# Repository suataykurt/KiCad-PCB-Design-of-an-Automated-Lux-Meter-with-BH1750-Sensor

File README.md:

# KiCad-PCB-Design-of-an-Automated-Lux-Meter

This repository contains the PCB design, schematic, and 3D visualization of a digital Lux Meter project, developed using KiCad. The system utilizes the **BH1750** ambient light sensor and an **I2C LCD** display for real-time light intensity monitoring.

## 📋 Project Overview
The project involves the complete design cycle for a light-measuring device, from schematic entry to PCB layout and 3D visualization. It demonstrates how to integrate I2C-based sensors with an Arduino-based controller to create a compact, functional measurement tool.

## 🛠 Design Highlights
* **Schematic Design:** Integration of the BH1750 light sensor, I2C LCD interface, and Arduino Nano controller.
* **PCB Layout:** Custom-designed PCB layout in KiCad, focusing on signal integrity and component placement.
* **3D Visualization:** In-depth examination of the 3D model for physical form factor and footprint validation.
* **Power Management:** On-board voltage regulation (AMS1117-5.0) ensuring stable operation.

## 🚀 Key Features
* **BH1750 Sensor Integration:** High-precision ambient light measurement.
* **Interactive Interface:** I2C LCD for clear, real-time data display.
* **Professional CAD Standards:** Industry-standard PCB design practices.

## 📂 Repository Contents
* `lux_olcer.kicad_sch`: Schematic file.
* `lux_olcer.kicad_pcb`: PCB layout design file.
* `lux_olcer.kicad_pro`: KiCad project settings.
* `BH1750.jpg` / `I2C-LCD.jpg`: Component reference images.

## 💡 How to Access
1. Clone the repository and open the project using **KiCad**.
2. Explore the PCB layout to view routing and component placement.
3. Use the KiCad 3D Viewer to inspect the hardware assembly models.

---
*Developed by Suat AYKURT | Zonguldak Bülent Ecevit University*

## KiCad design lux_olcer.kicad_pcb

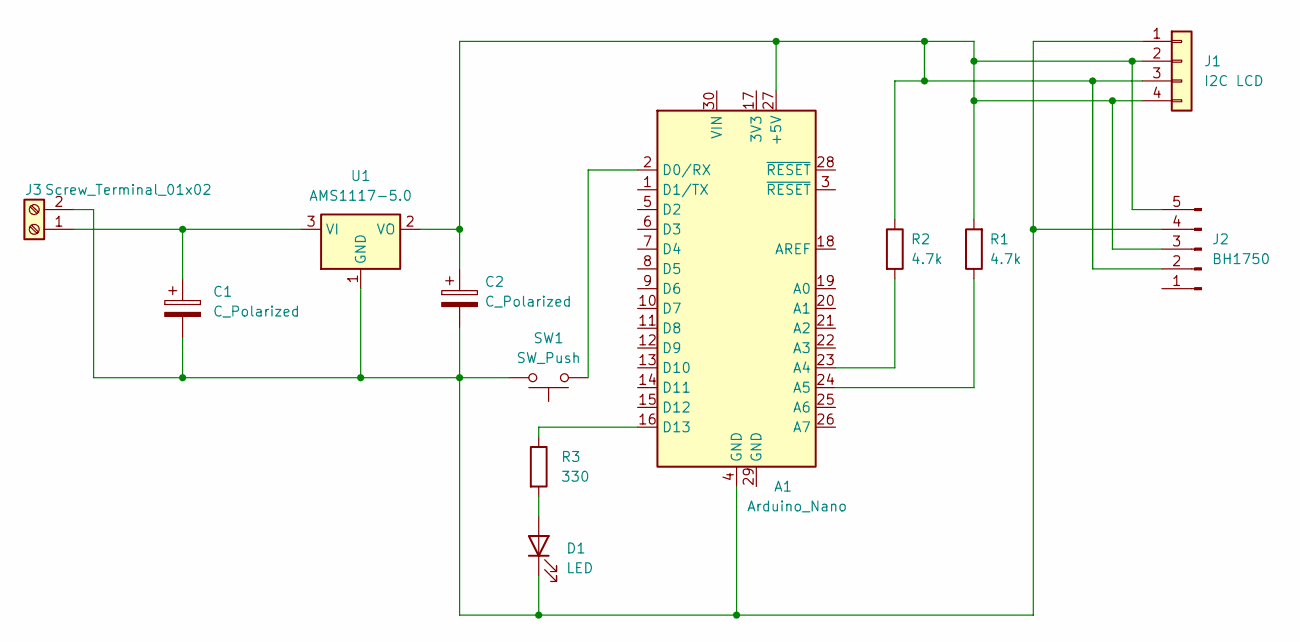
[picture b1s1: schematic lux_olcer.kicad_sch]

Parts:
A1: Arduino_Nano
C1, C2: C_Polarized; CP_Radial_D5.0mm_P2.00mm
D1: LED; LED_D5.0mm
J1: I2C LCD; PinHeader_1x04_P2.54mm_Vertical
J2: BH1750; PinHeader_1x05_P2.54mm_Vertical
J3: Screw_Terminal_01x02; TerminalBlock_Phoenix_MKDS-1,5-2_1x02_P5.00mm_Horizontal
R1, R2: 4.7k; R_Axial_DIN0207_L6.3mm_D2.5mm_P7.62mm_Horizontal
R3: 330; R_Axial_DIN0207_L6.3mm_D2.5mm_P7.62mm_Horizontal
SW1: SW_Push; SW_PUSH_6mm
U1: AMS1117-5.0; TO-220-3_Vertical

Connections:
unnamed: A1.27 (+5V), C2.1, J1.2, J1.3, J1.4, J2.2, J2.3, J2.5, R1.2, R2.1, U1.2 (VO)
unnamed: A1.23 (A4), R2.2
unnamed: A1.24 (A5), R1.1
unnamed: A1.2 (D0/RX), SW1.1
unnamed: A1.16 (D13), R3.1
unnamed: D1.2 (A), R3.2
unnamed: A1.4 (GND), C1.2, C2.2, D1.1 (K), J1.1, J2.4, J3.2, SW1.2, U1.1 (GND)
unnamed: C1.1, J3.1, U1.3 (VI)

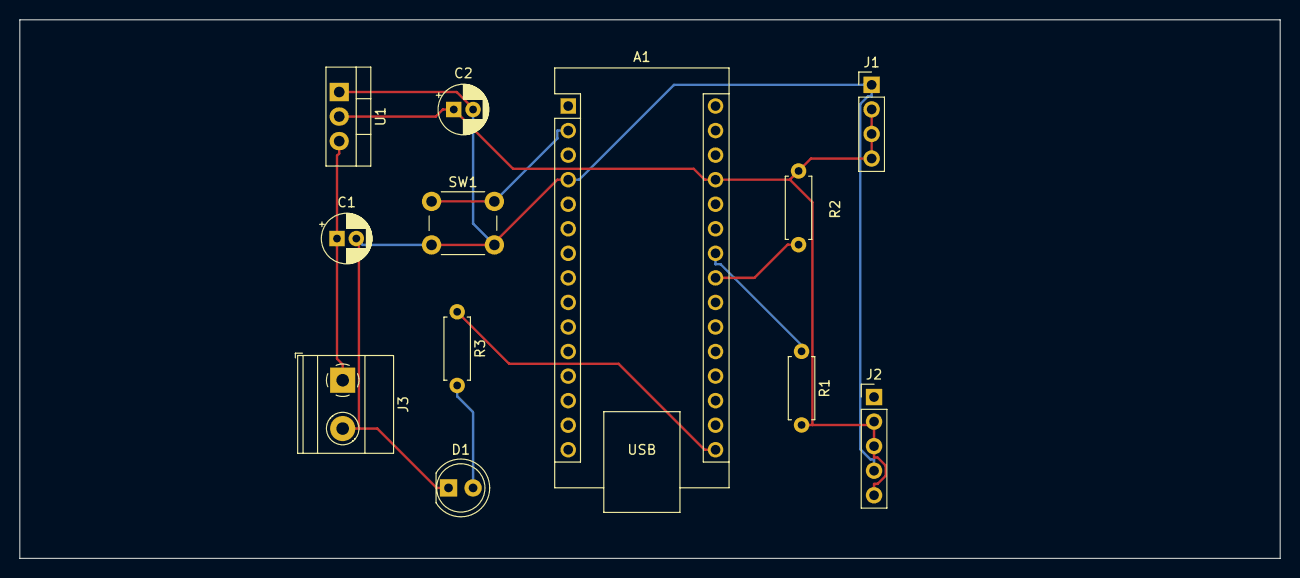
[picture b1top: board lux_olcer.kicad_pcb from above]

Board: 2 copper layers, 130.4 x 55.7 mm, 12 parts (0 on the bottom side), 8 nets.
